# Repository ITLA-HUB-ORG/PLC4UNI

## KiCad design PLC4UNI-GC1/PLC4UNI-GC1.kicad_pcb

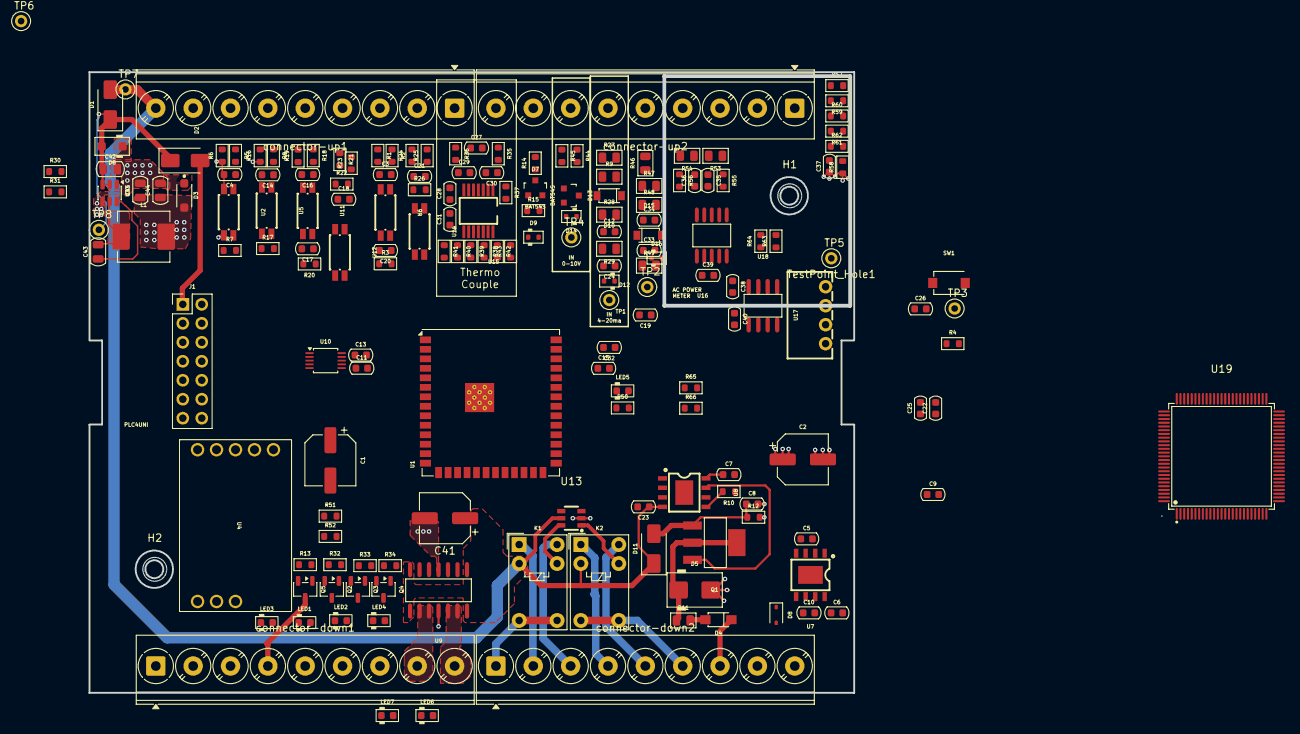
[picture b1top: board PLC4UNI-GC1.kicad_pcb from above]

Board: 4 copper layers, 102.4 x 83.1 mm, 177 parts (0 on the bottom side), 121 nets.

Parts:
C1, C2, C41: 47UF; CP_Elec_6.3x7.7
C3, C4, C14, C16, C18, C21: 2.2NF; C_0603_1608Metric
C5, C6, C7, C23: C_0603; C_0603_1608Metric
C8: 1uF; C_0603_1608Metric
C9, C15, C17, C19, C20, C22: 1NF; C_0603_1608Metric
C10: 100nF; C_0603_1608Metric
C11, C12, C13, C26, C28, C31, C32, C33, C38, C39, C40: 100NF; C_0603_1608Metric
C24, C34: 47PF; C_0603_1608Metric
C25: 100nf; C_0603_1608Metric
C27, C29, C30: 0.01UF; C_0603_1608Metric
C35, C36: 33NF; C_0603_1608Metric
C37: 68NF; C_0603_1608Metric
C42: 10uF; C_0805_2012Metric
C43: 100NF; C_0805_2012Metric
C44, C45: 22uF; C_0805_2012Metric
D1, D2: SS14; D_SMA
D3: SMF3.3; SMF3.3_SODFL3718X108N
D4: DSK120_C22466355; SOD-123FL_L2.7-W1.8-LS3.8-RD
D5: SMBJ28A; D_SMB
D6: SMF24CA; D_SOD-123F
D7, D13: BAT54S; SOT23-3_PO132
D8: SD12_SOD323; D_SOD-323
D9, D12, D14, D16: PESD5Z3.3; D_SOD-523
D10, D15: 1N5819HW-7-F; SOD-123_L2.7-W1.6-LS3.7-RD
D11: SMAJ12A; D_SMA
H1, H2: MountingHole; MountingHole_3.2mm_M3
J1: Conn_02x07_Odd_Even; PinHeader_2x07_P2.54mm_Vertical
K1, K2: G5V-1; Relay_SPDT_Omron_G5V-1
L1: 10uH; L_APV_APH0630
LED1, LED2, LED3, LED4, LED5, LED6, LED7: LED_0603_Red; LED_0603_1608Metric
Q1: NCE60P04R; SOT-223-3_L6.5-W3.4-P2.30-LS7.0-BR
Q2, Q3, Q4, Q5: ZXMS6004FFQTA; SOT-23-3
R1, R5, R8, R18, R21, R24: 3.6K; R_0603_1608Metric
R2, R6, R16, R19, R22, R25: 3.3K; R_0603_1608Metric
R3, R4, R7, R17, R20, R23, R26: 22K; R_0603_1608Metric
R9, R47: 120R; R_0805_2012Metric
R10, R13, R30, R31, R32, R33, R34, R51, R52: R_0603; R_0603_1608Metric
R11: 15R; R_0805_2012Metric
R12: 470K; R_0603_1608Metric
R14, R44, R50: 2.2K; R_0603_1608Metric
R15, R45: 1.05K; R_0603_1608Metric
R27, R46: 49.9R; R_0805_2012Metric
R28, R48: 47K; R_0805_2012Metric
R29, R49: 100K; R_0805_2012Metric
R35, R36: 0R; R_0603_1608Metric
R37: 20K; R_0603_1608Metric
R38, R39, R40, R41, R42, R43: 150; R_0603_1608Metric
R53, R54: 0.51; R_0805_2012Metric
R55, R56: 1K; R_0603_1608Metric
R57, R59, R60, R61, R62: 390K; R_0603_1608Metric
R58: 510; R_0603_1608Metric
R63, R64, R65, R66: 4.7K; R_0603_1608Metric
SW1: TS-1088-AR02016; SW-SMD_L3.9-W3.0-P4.45
TP1, TP2, TP3, TP4, TP5, TP6, TP7, TP8: TestPoint_Hole1; TestPoint_WireHole
U1: ESP32-S3-WROOM-1; ESP32-S3-WROOM-1U
U2, U5, U6, U11, U12, U14: AT3H4B-CUH-S; SSOP-4_L2.7-W4.6-P1.27-LS7.0-TL
U3: AP63203WU; TSOT-23-6
U4: RS485-PROTECT; RS-485-PROTECT
U7: GP8211S-TC50-EW; ESOP-8_L4.9-W3.9-P1.27-LS6.0-BL-EP
U8: GP8302-TC50-EW; ESOP-8_L4.9-W3.9-P1.27-LS6.0-BL-EP
U9: BTS723GWXUMA1; SOIC-14_L8.7-W3.9-P1.27-LS6.0-BL
U10: ADS1115IDGS; TSSOP-10_3x3mm_P0.5mm
U13: LK1802; SOT-23-6_L2.9-W1.6-P0.95-LS2.8-BR
U15: MAX31856MUD+; TSSOP-14_L5.0-W4.4-P0.65-LS6.4-BL
U16: BL0942; SSOP-10_L4.9-W3.9-P1.00-LS6.0-BL
U17: B0303S-1WR3_C7465185; PWRM-TH_BXXXXS-1WR3
U18: ISO7021DR; SOIC-8_L4.9-W3.9-P1.27-LS6.0-BL
U19: LCMXO256C-3TN100C; TQFP-100_L14.0-W14.0-P0.50-LS16.0-BL
connector-down1, connector-down2: Screw_Terminal_9_P5.00mm; TerminalBlock_Phoenix_PT-1,5-9-5.0-H_1x09_P5.00mm_Horizontal
connector-up1, connector-up2: Screw_Terminal_9_P5.00mm; TerminalBlock_Phoenix_PT-1,5-9-5.0-H_1x09_P5.00mm_Horizontal

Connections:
+3.3V: C1.1, C2.1, C13.1, C28.1, C31.1, C40.2, C44.1, C45.1, D3.A, D7.2 (cathode), D13.2 (cathode), J1.2, L1.2, R3.2, R4.2, R7.2, R17.2, R20.2, R23.2, R26.2, R65.2, R66.2, U1.2 (3V3), U3.1 (FB), U4.1 (VCC), U9.11 (SPU), U10.8 (VDD), U15.5 (AVDD), U15.8 (DVDD), U17.2 (+Vin), U18.1 (VCC1)
+5V: D2.2 (A), J1.1, TP6.1
+24V: C4.2, C5.1, C14.2, C16.2, C18.2, C23.1, C41.1, D1.2 (A), D11.1 (A1), K1.2, K2.2, R6.1, R13.1, R16.1, R19.1, R22.1, R30.1, R32.1, R33.1, R34.1, TP7.1, U2.2, U5.2, U7.4 (VCC), U8.4 (VCC), U9.1 (VBB), U9.7 (VBB), U9.8 (VBB), U9.14 (VBB), U11.2, U12.2, U13.5 (COM), connector-up1.9
/PowerSupply/sw: C43.2, L1.1, U3.5 (SW)
/PowerSupply/vdc_in: C42.1, D1.1 (K), D2.1 (K), D6.2 (A), TP8.1, U3.2 (EN), U3.3 (IN)
/control/CON-IN-4-20MA_1: R27.2, connector-up2.6
/control/CON-IN-4-20MA_2: R46.2, connector-up2.5
/control/CON-IN_CT_N: R54.2, R56.1, connector-up2.4
/control/CON-IN_CT_P: R53.1, R55.1, connector-up2.3
/control/CON-IN_VAC_P: R57.1, connector-up2.1
/control/CON_IN_0-10V_1: R14.1, connector-up2.8
/control/CON_IN_0-10V_2: R44.1, connector-up2.7
/control/CON_IN_NPN1: R5.1, connector-up1.7
/control/CON_IN_NPN2: R8.1, connector-up1.6
/control/CON_IN_NPN3: R18.1, connector-up1.5
/control/CON_IN_NPN4: R21.1, connector-up1.4
/control/CON_IN_PNP1: R1.1, connector-up1.3
/control/CON_IN_PNP2: R24.1, connector-up1.2
/control/CON_IN_TC+: R36.1, connector-up1.1
/control/CON_IN_TC-: R35.1, R37.1, connector-up2.9
/control/CON_OUT_0-10V: C10.1, D8.2 (A2), U7.6 (VOUT), connector-down2.8
/control/CON_OUT_4-20MA: D4.1 (C), connector-down2.7
/control/CON_OUT_NPN1: LED3.1 (K), Q5.3 (D), connector-down1.4
/control/CON_OUT_NPN2: LED1.1 (K), Q2.3 (D), connector-down1.5
/control/CON_OUT_NPN3: LED2.1 (K), Q3.3 (D), connector-down1.6
/control/CON_OUT_NPN4: LED4.1 (K), Q4.3 (D), connector-down1.7
/control/CON_OUT_PNP1: R51.1, U9.9 (OUT2), U9.10 (OUT2), connector-down1.8
/control/CON_OUT_PNP2: R52.1, U9.12 (OUT1), U9.13 (OUT1), connector-down1.9
/control/CON_OUT_RLY1_COM: K1.5, K1.6, connector-down2.1
/control/CON_OUT_RLY1_NC: K1.1, connector-down2.2
/control/CON_OUT_RLY1_NO: K1.10, connector-down2.3
/control/CON_OUT_RLY2_COM: K2.5, K2.6, connector-down2.6
/control/CON_OUT_RLY2_NC: K2.1, connector-down2.4
/control/CON_OUT_RLY2_NO: K2.10, connector-down2.5
/control/CON_RS485_A: U4.7 (A), connector-down1.2
/control/CON_RS485_B: U4.8 (B), connector-down1.3
/control/CON_RS485_G: U4.6 (RGND), connector-down1.1
/control/EMRX: R66.1, U1.36 (RXD0), U18.2 (OUTA)
/control/EM_TX: R65.1, U1.37 (TXD0), U18.3 (INB)
/control/EN: C26.2, R4.1, SW1.1, U1.3 (EN)
/control/GPIO1: J1.11, U1.8 (IO15)
/control/GPIO2: J1.12, U1.9 (IO16)
/control/IN-0-10V1/COM: C32.2, D14.2 (A), R45.2
/control/IN-0-10V1/OUT3V: C32.1, D13.3 (AK), D14.1 (K), R44.2, R45.1, TP4.1, U10.7 (AIN3)
/control/IN-0-10V/COM: C11.2, D9.2 (A), R15.2
/control/IN-0-10V/OUT3V: C11.1, D7.3 (AK), D9.1 (K), R14.2, R15.1, TP3.1, U10.6 (AIN2)
/control/IN-4-20MA1/OUT: C34.1, D16.1 (K), R49.1, TP2.1, U10.5 (AIN1)
/control/IN-4-20MA/OUT: C24.1, D12.1 (K), R29.1, TP1.1, U10.4 (AIN0)
/control/IN_NPN1: C9.1, R7.1, U1.27 (IO0), U2.4
/control/IN_NPN2: C15.1, R17.1, U1.39 (IO1), U5.4
/control/IN_NPN3: C17.1, R20.1, U1.38 (IO2), U11.4
/control/IN_NPN4: C19.1, R23.1, U1.15 (IO3), U12.4
/control/IN_PNP1: C20.1, R3.1, U1.4 (IO4), U6.4
/control/IN_PNP2: C22.1, R26.1, U1.5 (IO5), U14.4
/control/IN_VDC_ADC: C25.1, R30.2, R31.1, U1.6 (IO6)
/control/LED_INFO: R50.2, U1.23 (IO21)
/control/OUT_NPN1: Q5.1 (IN), U1.31 (IO38)
/control/OUT_NPN2: Q2.1 (IN), U1.32 (IO39)
/control/OUT_NPN3: Q3.1 (IN), U1.33 (IO40)
/control/OUT_NPN4: Q4.1 (IN), U1.34 (IO41)
/control/OUT_PNP1: U1.16 (IO46), U9.2 (IN1)
/control/OUT_PNP2: U1.24 (IO47), U9.6 (IN2)
/control/OUT_RLY1: U1.35 (IO42), U13.3 (1B)
/control/OUT_RLY2: U1.26 (IO45), U13.4 (2B)
/control/TEMP_CS: R41.2, U1.25 (IO48)
/control/clk: J1.9, R40.2, U1.22 (IO14)
/control/cs: J1.3, U1.19 (IO11)
/control/i2c_scl: J1.10, U1.11 (IO18), U7.1 (SCLK), U8.1 (SLCK), U10.10 (SCL)
/control/i2c_sda: J1.8, U1.10 (IO17), U7.2 (SDA), U8.2 (SDA), U10.9 (SDA)
/control/miso: J1.7, R39.2, U1.20 (IO12)
/control/mosi: J1.5, R38.2, U1.21 (IO13)
/control/usb+: J1.4, U1.14 (USB_D+)
/control/usb-: J1.6, U1.13 (USB_D-)
Earth: C35.1, C36.2, C37.1, C38.1, C39.1, R53.2, R54.1, R58.1, U16.5 (GND), U16.7 (SEL), U17.3 (-Vout), U18.5 (GND2), connector-up2.2
GND: C1.2, C2.2, C3.2, C5.2, C6.2, C7.2, C8.2, C9.2, C10.2, C12.2, C13.2, C15.2, C17.2, C19.2, C20.2, C21.2, C22.2, C23.2, C24.2, C25.2, C26.1, C28.2, C29.2, C30.2, C31.2, C33.2, C34.2, C40.1, C41.2, C42.2, C44.2, C45.2, D3.C, D5.2 (A), D6.1 (K), D7.1 (Anode), D8.1 (A1), D10.2 (A), D12.2 (A), D13.1 (Anode), D15.2 (A), D16.2 (A), J1.13, J1.14, LED5.1 (K), LED6.1 (K), LED7.1 (K), Q2.2 (OUT), Q3.2 (OUT), Q4.2 (OUT), Q5.2 (OUT), R2.1, R9.1, R10.2, R12.2, R25.1, R31.2, R47.1, SW1.2, U1.1 (GND), U1.40 (GND), U1.41 (GND), U2.3, U3.4 (GND), U4.2 (GND), U5.3, U6.2, U6.3, U7.5 (GND), U7.9 (EP), U8.5 (GND), U8.9 (EP), U9.4 (GND), U10.1 (ADDR), U10.3 (GND), U11.3, U12.3, U13.2 (E), U14.2, U14.3, U15.1 (AGND), U15.14 (DGND), U17.1 (-Vin), U18.4 (GND1), connector-down2.9, connector-up1.8
unnamed: C3.1, R1.2, R2.2, U6.1
unnamed: C4.1, R5.2, R6.2, U2.1
unnamed: C12.1, R28.1, R29.2
unnamed: C14.1, R8.2, R16.2, U5.1
unnamed: C16.1, R18.2, R19.2, U11.1
unnamed: C18.1, R21.2, R22.2, U12.1
unnamed: C21.1, R24.2, R25.2, U14.1
unnamed: C33.1, R48.1, R49.2
unnamed: D4.2 (A), R11.2
unnamed: D5.1 (K), Q1.2, Q1.4, R11.1
unnamed: D10.1 (K), R9.2, R27.1, R28.2
unnamed: C8.1, D11.2 (A2), Q1.1, R12.1
unnamed: D15.1 (K), R46.1, R47.2, R48.2
unnamed: LED1.2 (A), R32.2
unnamed: LED2.2 (A), R33.2
unnamed: LED3.2 (A), R13.2
unnamed: LED4.2 (A), R34.2
unnamed: LED5.2 (A), R50.1
unnamed: LED6.2 (A), R51.2
unnamed: LED7.2 (A), R52.2
unnamed: R57.2, R59.1
unnamed: R59.2, R60.1
unnamed: R60.2, R61.1
unnamed: R61.2, R62.1
unnamed: C43.1, U3.6 (BST)
unnamed: C6.1, U7.8 (V5V)
unnamed: Q1.3, U8.7 (IOUT)
unnamed: R10.1, U8.6 (SET)
unnamed: C7.1, U8.8 (V5V)
unnamed: K2.9, U13.1 (1C)
unnamed: K1.9, U13.6 (2C)
unnamed: R37.2, U15.2 (BIAS)
unnamed: R40.1, U15.10 (SCK)
unnamed: R38.1, U15.12 (SDI)
unnamed: R39.1, U15.11 (SDO)
unnamed: C27.2, C29.1, R36.2, U15.4 (T+)
unnamed: C27.1, C30.1, R35.2, U15.3 (T-)
unnamed: R41.1, U15.9 (~CS)
unnamed: R43.1, U15.7 (~DRDY)
unnamed: R42.1, U15.13 (~FAULT)
unnamed: C36.1, R56.2, U16.3 (IN)
unnamed: C35.2, R55.2, U16.2 (IP)
unnamed: R63.1, U16.9 (RX/SDI), U18.6 (OUTB)
unnamed: R64.1, U16.10 (TX/SDO), U18.7 (INA)
unnamed: C37.2, R58.2, R62.2, U16.4 (VP)
VCC: C38.2, C39.2, R63.2, R64.2, TP5.1, U16.1 (VDD), U16.8 (SCLK_BPS), U17.4 (+Vout), U18.8 (VCC2)

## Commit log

2026-02-20 Actualizado al dia de hoy
2026-03-05 Colocadas el 80% de las piezas
2026-03-05 Avances en colocacion de piezas y verificacion de componentes
2026-03-06 Eliminados los archivos CAD, para ser colocados en su repositorio dedicado
